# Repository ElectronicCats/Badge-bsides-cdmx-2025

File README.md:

# Security BSides CDMX 2025 Badge

## Technology

- Puya PY32F030F28U6TR
- Neopixels
- Display OLED
- 2x AAA Battery Holder
- Shitty Addon Connector

## Getting Started

Your badge comes with a pre-installed firmware, but in case you need to reprogram it, you can use the binaries from the release section.

If you want to build your own firmware, check out the [README](firmware/README.md) in the firmware folder.

## Gratitude
Do you want to say thank you? Tag these companies on social networks and show them your badge, thanks to them it is possible

- [Electronic Cats](https://electroniccats.com/)
- [BSides CDMX](https://bsidescdmx.org/)

## License

Electronic Cats invests time and resources providing this open source design, please support Electronic Cats and open-source hardware by purchasing products from Electronic Cats!

Designed by Electronic Cats.

Hardware released under an CERN Open Hardware Licence v1.2. See the LICENSE_HARDWARE file for more information.

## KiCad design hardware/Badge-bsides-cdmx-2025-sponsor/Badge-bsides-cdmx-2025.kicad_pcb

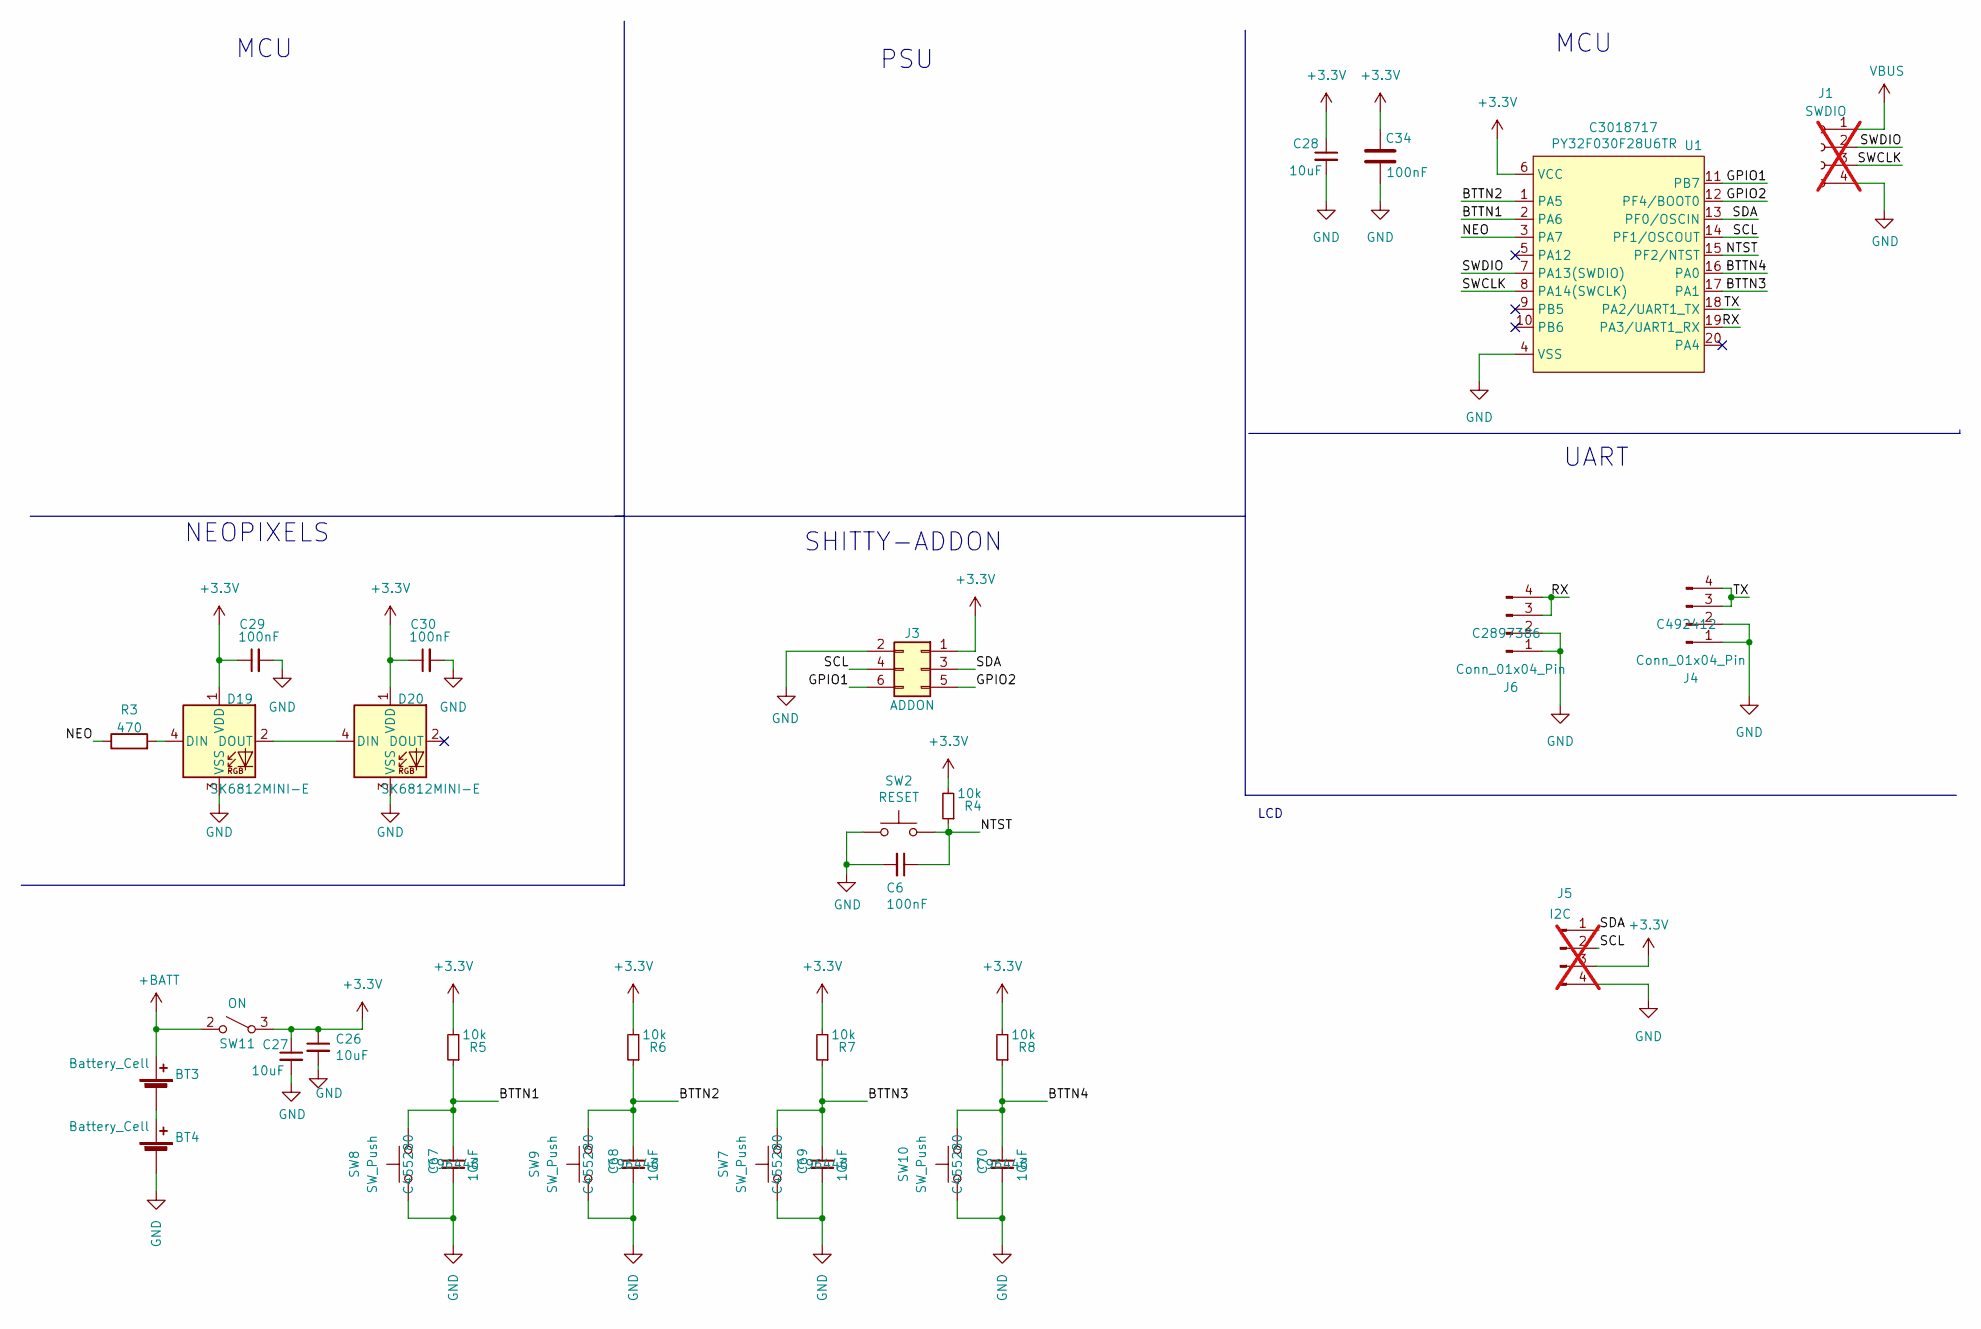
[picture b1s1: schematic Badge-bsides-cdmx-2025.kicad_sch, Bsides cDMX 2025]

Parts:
BT3, BT4: Battery_Cell; BatteryHolder_Keystone_2466_1xAAA; LCSC# C5290189
C6, C29, C30, C34: 100nF; C_0603_1608Metric; LCSC# C66501
C26, C27, C28, C67, C68, C69, C70: 10uF; C_0603_1608Metric; LCSC# C96446
D19, D20: SK6812MINI-E; LED_SK6812-E; LCSC# C5149201
J1: SWDIO; PinHeader_1x04_P2.54mm_Vertical; not fitted
J3: ADDON; PinSocket_2x03_P2.54mm_Vertical_SMD; LCSC# C3975148
J4: Conn_01x04_Pin; PinHeader_1x04_P2.54mm_Horizontal; LCSC# C492412
J5: I2C; PinSocket_1x04_P2.54mm_Vertical; not fitted
J6: Conn_01x04_Pin; PinSocket_1x04_P2.54mm_Horizontal; LCSC# C2897386
R3: 470; R_0603_1608Metric; LCSC# C114669
R4, R5, R6, R7, R8: 10k; R_0603_1608Metric; LCSC# C99198
SW2: RESET; SW_SPST_TL3342; LCSC# C318884
SW7, SW8, SW9, SW10: SW_Push; TS1088R02026; LCSC# C455280
SW11: ON; JS102011SAQN; LCSC# C221660
U1: PY32F030F28U6TR; QFN-20-1EP_3x3mm_P0.4mm_EP1.65x1.65mm_ThermalVias; LCSC# C3018717

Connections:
+3.3V: C26.1, C27.1, C28.1, C29.1, C30.1, C34.1, D19.1 (VDD), D20.1 (VDD), J3.1, J5.3, R4.2, R5.2, R6.2, R7.2, R8.2, SW11.3 (A), U1.6 (VCC)
+BATT: BT3.2 (+), SW11.2 (B)
/BTTN1: C67.1, R5.1, SW8.2, U1.2 (PA6)
/BTTN2: C68.1, R6.1, SW9.2, U1.1 (PA5)
/BTTN3: C69.1, R7.1, SW7.2, U1.17 (PA1)
/BTTN4: C70.1, R8.1, SW10.2, U1.16 (PA0)
/GPIO1: J3.6, U1.11 (PB7)
/GPIO2: J3.5, U1.12 (PF4/BOOT0)
/NEO: R3.1, U1.3 (PA7)
/NTST: C6.1, R4.1, SW2.2, U1.15 (PF2/NTST)
/RX: J6.3, J6.4, U1.19 (PA3/UART1_RX)
/SCL: J3.4, J5.2, U1.14 (PF1/OSCOUT)
/SDA: J3.3, J5.1, U1.13 (PF0/OSCIN)
/SWCLK: J1.3, U1.8 (PA14(SWCLK))
/SWDIO: J1.2, U1.7 (PA13(SWDIO))
/TX: J4.3, J4.4, U1.18 (PA2/UART1_TX)
GND: BT4.2 (-), C6.2, C26.2, C27.2, C28.2, C29.2, C30.2, C34.2, C67.2, C68.2, C69.2, C70.2, D19.3 (VSS), D20.3 (VSS), J1.4, J3.2, J4.1, J4.2, J5.4, J6.1, J6.2, SW2.1, SW7.1, SW8.1, SW9.1, SW10.1, U1.4 (VSS), U1.21 (VSS)
unnamed: BT3.1 (-), BT4.1 (+)
unnamed: D19.4 (DIN), R3.2
unnamed: D19.2 (DOUT), D20.4 (DIN)
VBUS: J1.1

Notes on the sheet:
LCD
SHITTY-ADDON
MCU
UART
PSU
NEOPIXELS

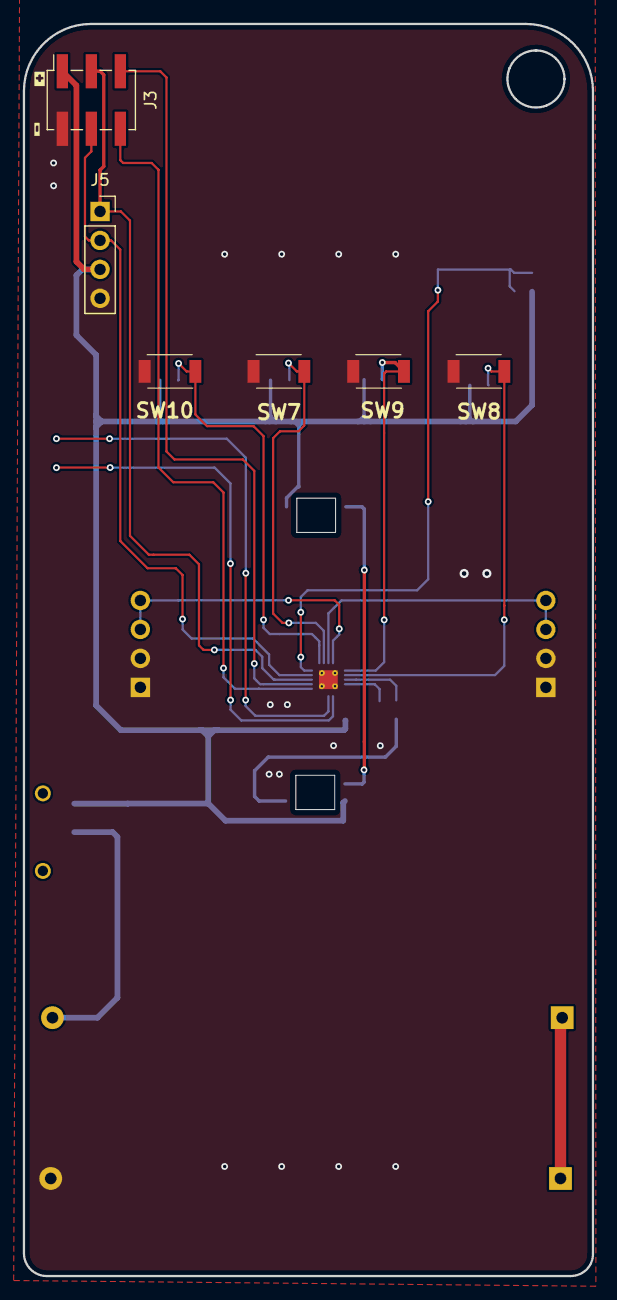
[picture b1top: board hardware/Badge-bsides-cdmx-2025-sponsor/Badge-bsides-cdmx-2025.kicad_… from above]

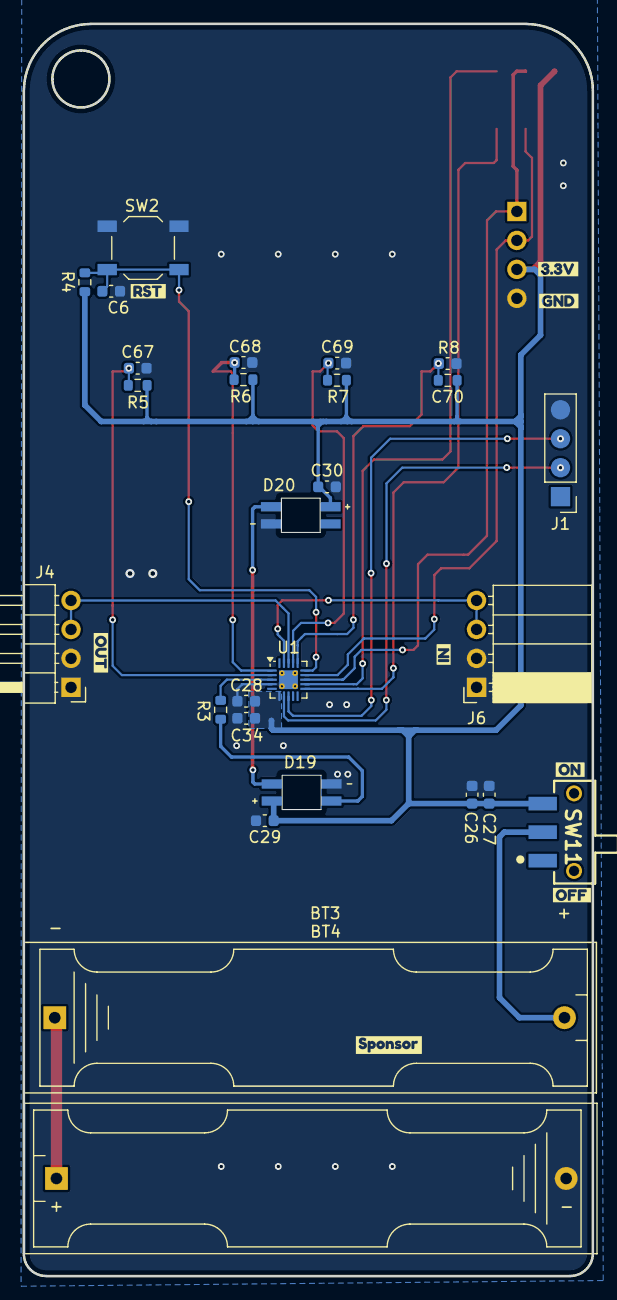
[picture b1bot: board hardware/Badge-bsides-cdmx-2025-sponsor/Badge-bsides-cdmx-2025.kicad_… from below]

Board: 2 copper layers, 49.9 x 109.8 mm, 43 parts (35 on the bottom side), 20 nets.

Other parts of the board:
kibuzzard-6841DC13: G***; kibuzzard-6841DC13
kibuzzard-6842C085: G***; kibuzzard-6842C085
kibuzzard-6842ED2D: G***; kibuzzard-6842ED2D
kibuzzard-6842ED45: G***; kibuzzard-6842ED45
kibuzzard-6842EE28: G***; kibuzzard-6842EE28
kibuzzard-6842EE36: G***; kibuzzard-6842EE36
kibuzzard-684316B7: G***; kibuzzard-684316B7
kibuzzard-684316C2: G***; kibuzzard-684316C2
kibuzzard-684316CB: G***; kibuzzard-684316CB
kibuzzard-684316D5: G***; kibuzzard-684316D5

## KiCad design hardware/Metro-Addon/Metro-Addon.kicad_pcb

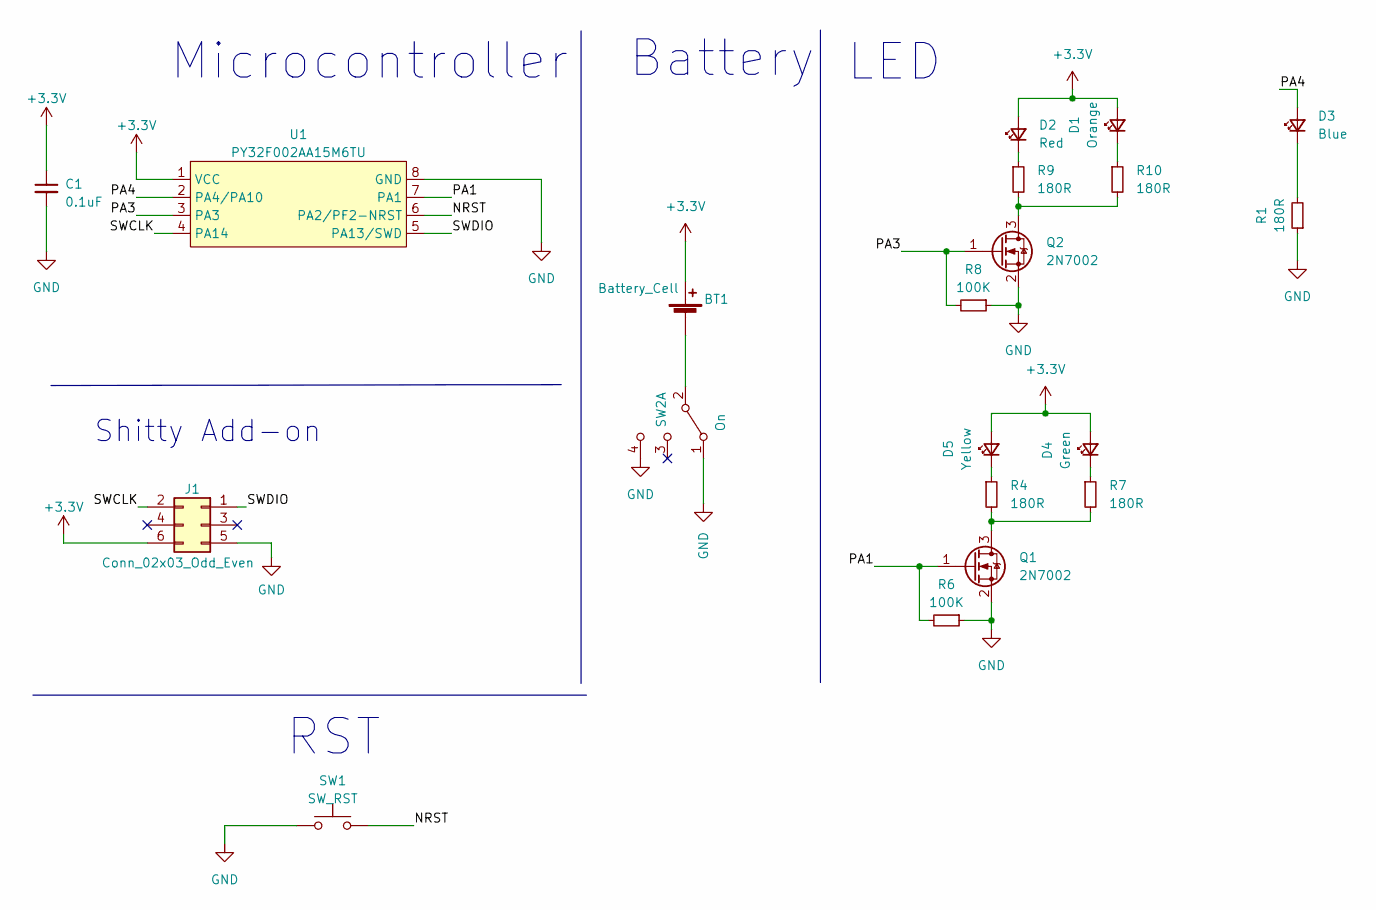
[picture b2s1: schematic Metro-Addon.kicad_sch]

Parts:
BT1: Battery_Cell; BAT-HLD-001; LCSC# C964833
C1: 0.1uF; C_0805_2012Metric; LCSC# C235731
D1: Orange; LED_0805_2012Metric; LCSC# C434437
D2: Red; LED_0805_2012Metric; LCSC# C965812
D3: Blue; LED_0805_2012Metric; LCSC# C205441
D4: Green; LED_0805_2012Metric; LCSC# C965815
D5: Yellow; LED_0805_2012Metric; LCSC# C84261
J1: Conn_02x03_Odd_Even; B-2100N06P-B111_CKM; LCSC# C780054
Q1, Q2: 2N7002; SOT-23; LCSC# C8545
R1, R4, R7, R9, R10: 180R; R_0805_2012Metric; LCSC# C1339
R6, R8: 100K; R_0805_2012Metric; LCSC# C96346
SW1: SW_RST; SW_SPST_TL3342; LCSC# C318889
SW2: On; MSK12C02; LCSC# C431540
U1: PY32F002AA15M6TU; PY32F002AL15S6TU; LCSC# C5292060

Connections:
+3.3V: BT1.2 (+), C1.1, D1.2 (A), D2.2 (A), D4.2 (A), D5.2 (A), J1.6, U1.1 (VCC)
/NRST: SW1.2, U1.6 (PA2/PF2-NRST)
/PA1: Q1.1 (G), R6.2, U1.7 (PA1)
/PA3: Q2.1 (G), R8.2, U1.3 (PA3)
/PA4: D3.2 (A), U1.2 (PA4/PA10)
/SWCLK: J1.2, U1.4 (PA14)
/SWDIO: J1.1, U1.5 (PA13/SWD)
GND: C1.2, J1.5, Q1.2 (S), Q2.2 (S), R1.1, R6.1, R8.1, SW1.1, SW2.1 (A), SW2.4 (C), U1.8 (GND)
unnamed: BT1.1 (-), SW2.2 (B)
unnamed: D1.1 (K), R10.1
unnamed: D2.1 (K), R9.1
unnamed: D3.1 (K), R1.2
unnamed: D4.1 (K), R7.1
unnamed: D5.1 (K), R4.1
unnamed: Q1.3 (D), R4.2, R7.2
unnamed: Q2.3 (D), R9.2, R10.2

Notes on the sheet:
Microcontroller
LED
RST
Battery
Shitty Add-on

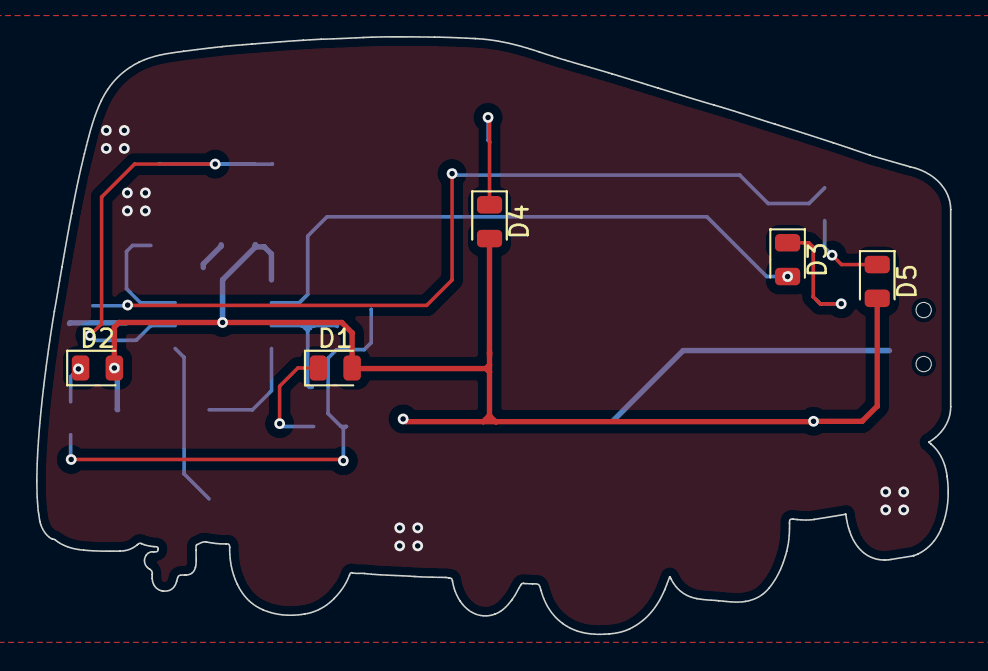
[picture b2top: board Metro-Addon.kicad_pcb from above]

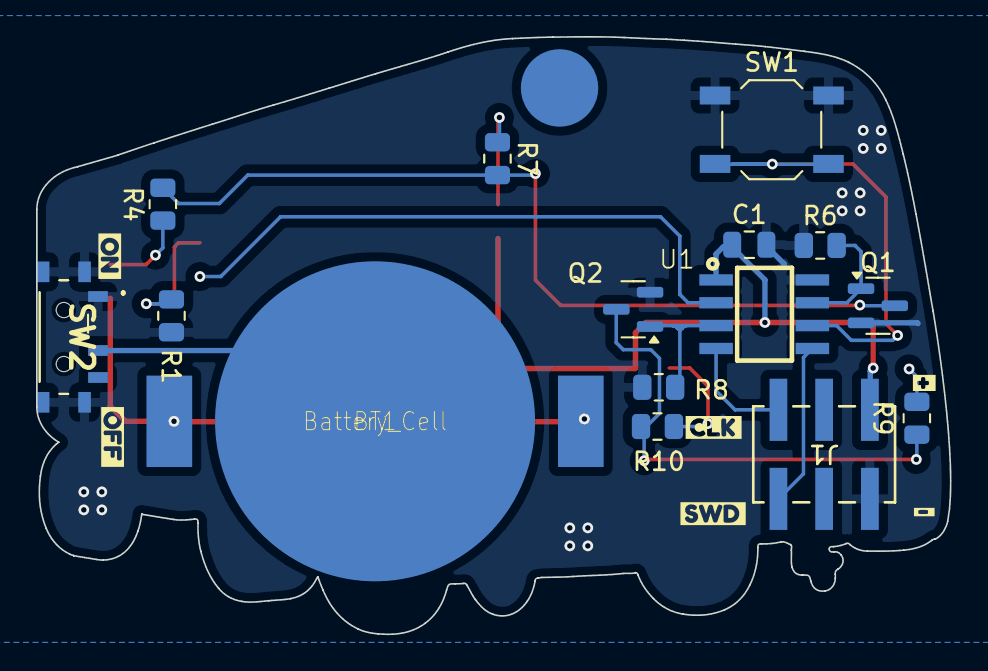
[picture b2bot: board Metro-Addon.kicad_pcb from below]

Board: 2 copper layers, 50.8 x 33.2 mm, 26 parts (21 on the bottom side), 16 nets.

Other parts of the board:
kibuzzard-684752D8: G***; kibuzzard-684752D8
kibuzzard-684752FB: G***; kibuzzard-684752FB
kibuzzard-684756AF: G***; kibuzzard-684756AF
kibuzzard-684756BD: G***; kibuzzard-684756BD
kibuzzard-684756E4: G***; kibuzzard-684756E4
kibuzzard-684756F0: G***; kibuzzard-684756F0

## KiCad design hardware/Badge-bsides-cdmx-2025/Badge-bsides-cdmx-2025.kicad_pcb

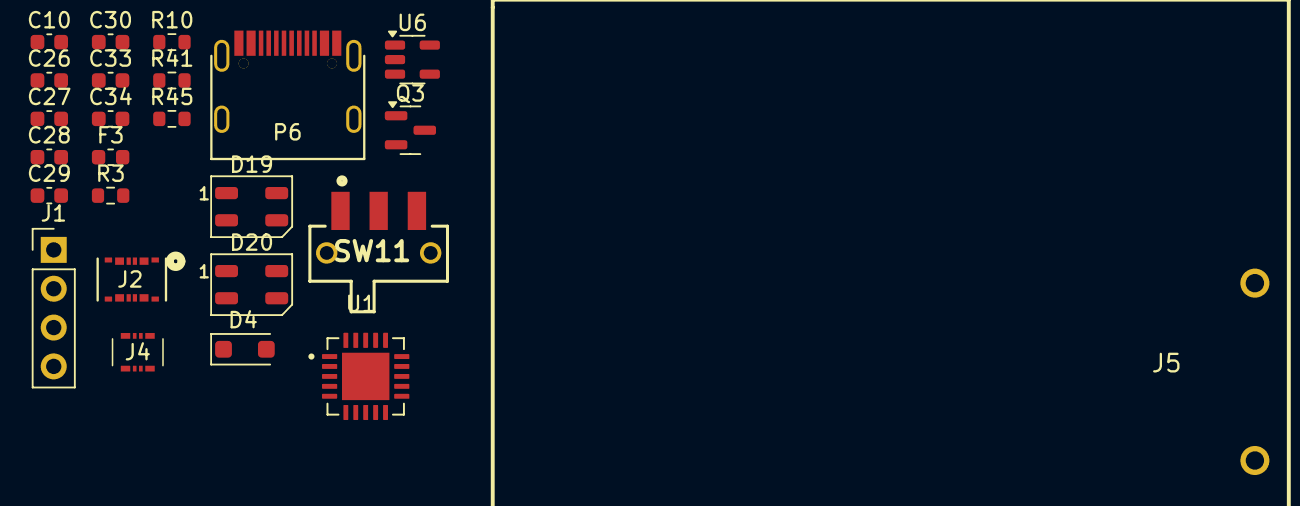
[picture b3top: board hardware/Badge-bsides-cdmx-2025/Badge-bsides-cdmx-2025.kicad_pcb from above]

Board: 2 copper layers, 25 parts (0 on the bottom side), 17 nets, no tracks yet.

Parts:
C10, C26, C27, C28: 10uF; C_0603_1608Metric
C29, C30, C33, C34: 100nF; C_0603_1608Metric
D4: MBR120; D_SOD-123F
D19, D20: WS2812B; LED_WS2812B-Mini_PLCC4_3.5x3.5mm
F3: 750mA; Fuse_0603_1608Metric
J1: SWDIO; PinHeader_1x04_P2.54mm_Vertical
J2: Conn_01x08_Pin; CONN8_505004-0812_MOL
J4: Conn_01x02_Pin; 5050060812
J5: Battery; BAT-TH_BH-AAA-A1AJ024
P6: USB_C_Plug_USB2.0; C393939
Q3: DMG3415U-7; SOT-23
R3: 1K; R_0603_1608Metric
R10: 100K; R_0603_1608Metric
R41, R45: 5k1; R_0603_1608Metric
SW11: ON; JS102011SAQN
U1: PY32F030F28U6TR; QFN65P500X500X80-21N
U6: AP2112K-3.3; SOT-23-5

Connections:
+3.3V: C28.1, C34.1, U1.6 (VCC)
+3V3: C26.1, C29.1, C30.1, D19.1 (VDD), D20.1 (VDD), U6.5 (VOUT)
+BATT: J5.1, Q3.3 (D)
/NEOPIXELES: R3.1, U1.3 (PA7)
/RX: J2.2, J2.3, J2.6, J2.7, U1.19 (PA3/UART1_RX)
/SWCLK: J1.3, U1.8 (PA14(SWCLK))
/SWDIO: J1.2, U1.7 (PA13(SWDIO))
/TX: J4.2, J4.3, J4.6, J4.7, U1.18 (PA2/UART1_TX)
GND: C10.2, C26.2, C27.2, C28.2, C29.2, C30.2, C33.2, C34.2, D19.3 (VSS), D20.3 (VSS), J1.4, J2.1, J2.4, J2.5, J2.8, J4.1, J4.4, J4.5, J4.8, J5.2, P6.A1 (GND), P6.S1 (SHIELD), R10.2, R41.1, R45.1, U1.4 (VSS), U6.2 (GND)
unnamed: D4.1 (K), Q3.2 (S), SW11.3 (A)
unnamed: D19.4 (DIN), R3.2
unnamed: D19.2 (DOUT), D20.4 (DIN)
unnamed: F3.1, P6.A4 (VBUS)
unnamed: P6.A5 (CC), R41.2
unnamed: P6.B5 (VCONN), R45.2
unnamed: C10.1, SW11.2 (B), U6.1 (VIN), U6.3 (EN)
VBUS: C33.1, D4.2 (A), F3.2, J1.1, Q3.1 (G), R10.1

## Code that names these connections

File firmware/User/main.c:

/***
 * Demo: I2C - SSD1306 OLED
 *
 * PY32          SSD1306
 *  PF1/PA9       SCL
 *  PF0/PA10      SDA
 */
#include "main.h"
#include <string.h>
#include "bitmaps.h"
#include "buttons.h"
#include "menu.h"
#include "py32f0xx_bsp_clock.h"
#include "py32f0xx_bsp_printf.h"
#include "ssd1306.h"
#include "ws2812_spi.h"

#define I2C_ADDRESS 0xA0 /* host/client address */
#define I2C_STATE_READY 0
#define I2C_STATE_BUSY_TX 1
#define I2C_STATE_BUSY_RX 2

__IO uint32_t i2cState = I2C_STATE_READY;

static void APP_I2C_Config(void);
static void APP_GPIO_Config(void);
static void APP_SPIConfig(void);

int main(void) {
  uint8_t i = 0, r = 0, g = 0x60, b = 0xC0;
  BSP_RCC_HSI_24MConfig();

  BSP_USART_Config(115200);
  printf("I2C Demo: \r\nClock: %ld\r\n", SystemCoreClock);

  APP_I2C_Config();
  APP_GPIO_Config();
  APP_SPIConfig();

  uint8_t res = SSD1306_Init();
  printf("OLED init: %s\n", res == 0 ? "ERROR" : "OK");

  SSD1306_UpdateScreen();
  SSD1306_DrawBitmap(epd_bitmap_bsides_logo, 0, 0, 128, 32);
  SSD1306_UpdateScreen();

  // Wait for any button press
  while (1) {
    if (is_btn_back_pressed()) {
      break;
    }
    if (is_btn_enter_pressed()) {
      break;
    }
    if (is_btn_down_pressed()) {
      break;
    }
    if (is_btn_up_pressed()) {
      break;
    }
    i = (i + 1) % WS2812_NUM_LEDS;
    ws2812_pixel(i, r++, g++, b++);
    LL_mDelay(10);
  }
  
  while (1) {
    Menu_UpdateAndRender();
  }
}

static void APP_GPIO_Config(void) {
  LL_GPIO_InitTypeDef GPIO_InitStruct = {0};

  LL_IOP_GRP1_EnableClock(LL_IOP_GRP1_PERIPH_GPIOA);

  /*
   * Buttons:
   * DOWN:  PA0
   * UP:    PA1
   * BACK:  PA5
   * ENTER: PA6
   */
  GPIO_InitStruct.Pin = LL_GPIO_PIN_0 | LL_GPIO_PIN_1 | LL_GPIO_PIN_5 | LL_GPIO_PIN_6;
  GPIO_InitStruct.Mode = LL_GPIO_MODE_INPUT;
  GPIO_InitStruct.Pull = LL_GPIO_PULL_UP;
  LL_GPIO_Init(GPIOA, &GPIO_InitStruct);
}

static void APP_I2C_Config(void) {
  LL_GPIO_InitTypeDef GPIO_InitStruct = {0};

  LL_IOP_GRP1_EnableClock(LL_IOP_GRP1_PERIPH_GPIOF);
  LL_APB1_GRP1_EnableClock(LL_APB1_GRP1_PERIPH_I2C1);

  /**
   * SCL: PF1 & AF_12, PA9 & AF_6
   * SDA: PF0 & AF_12, PA10 & AF_6
   *
   * Change pins to PF1 / PF0 for parts have no PA9 / PA10
   */
  // PF1 SCL
  GPIO_InitStruct.Pin = LL_GPIO_PIN_1;
  GPIO_InitStruct.Mode = LL_GPIO_MODE_ALTERNATE;
  GPIO_InitStruct.Speed = LL_GPIO_SPEED_FREQ_HIGH;
  GPIO_InitStruct.OutputType = LL_GPIO_OUTPUT_OPENDRAIN;
  GPIO_InitStruct.Pull = LL_GPIO_PULL_UP;
  GPIO_InitStruct.Alternate = LL_GPIO_AF_12;
  LL_GPIO_Init(GPIOF, &GPIO_InitStruct);

  // PF0 SDA
  GPIO_InitStruct.Pin = LL_GPIO_PIN_0;
  GPIO_InitStruct.Alternate = LL_GPIO_AF_12;
  LL_GPIO_Init(GPIOF, &GPIO_InitStruct);

  LL_APB1_GRP1_ForceReset(LL_APB1_GRP1_PERIPH_I2C1);
  LL_APB1_GRP1_ReleaseReset(LL_APB1_GRP1_PERIPH_I2C1);

  LL_I2C_InitTypeDef I2C_InitStruct;
  /*
   * Clock speed:
   * - standard = 100khz, if PLL is on, set system clock <= 16MHz, or i2c cannot work normally
   * - fast     = 400khz
   */
  I2C_InitStruct.ClockSpeed = LL_I2C_MAX_SPEED_FAST;
  I2C_InitStruct.DutyCycle = LL_I2C_DUTYCYCLE_16_9;
  I2C_InitStruct.OwnAddress1 = I2C_ADDRESS;
  I2C_InitStruct.TypeAcknowledge = LL_I2C_NACK;
  LL_I2C_Init(I2C1, &I2C_InitStruct);

  /* Enale clock stretch (reset default: on) */
  // LL_I2C_EnableClockStretching(I2C1);

  /* Enable general call (reset default: off) */
  // LL_I2C_EnableGeneralCall(I2C1);
}

void APP_I2C_Transmit(uint8_t devAddress, uint8_t memAddress, uint8_t* pData, uint16_t len) {
  while (i2cState == I2C_STATE_BUSY_TX)
    ;

  LL_I2C_DisableBitPOS(I2C1);

  i2cState = I2C_STATE_BUSY_TX;

  /* Start */
  LL_I2C_GenerateStartCondition(I2C1);
  while (LL_I2C_IsActiveFlag_SB(I2C1) != 1)
    ;
  /* Send slave address */
  LL_I2C_TransmitData8(I2C1, (devAddress & (uint8_t)(~0x01)));
  while (LL_I2C_IsActiveFlag_ADDR(I2C1) != 1)
    ;
  LL_I2C_ClearFlag_ADDR(I2C1);

  /* Send memory address */
  LL_I2C_TransmitData8(I2C1, memAddress);
  while (LL_I2C_IsActiveFlag_BTF(I2C1) != 1)
    ;

  /* Transfer data */
  while (len > 0) {
    while (LL_I2C_IsActiveFlag_TXE(I2C1) != 1)
      ;
    LL_I2C_TransmitData8(I2C1, *pData++);
    len--;

    if ((LL_I2C_IsActiveFlag_BTF(I2C1) == 1) && (len != 0U)) {
      LL_I2C_TransmitData8(I2C1, *pData++);
      len--;
    }

    while (LL_I2C_IsActiveFlag_BTF(I2C1) != 1)
      ;
  }

  /* Stop */
  LL_I2C_GenerateStopCondition(I2C1);
  i2cState = I2C_STATE_READY;
}

uint8_t SPI_TxRxByte(uint8_t data)
{
  uint8_t SPITimeout = 0xFF;
  /* Check the status of Transmit buffer Empty flag */
  while (READ_BIT(SPI1->SR, SPI_SR_TXE) == RESET)
  {
    if (SPITimeout-- == 0) return 0;
  }
  LL_SPI_TransmitData8(SPI1, data);
  SPITimeout = 0xFF;
  while (READ_BIT(SPI1->SR, SPI_SR_RXNE) == RESET)
  {
    if (SPITimeout-- == 0) return 0;
  }
  // Read from RX buffer
  return LL_SPI_ReceiveData8(SPI1);
}

static void APP_SPIConfig(void)
{
  LL_SPI_InitTypeDef SPI_InitStruct = {0};
  LL_GPIO_InitTypeDef GPIO_InitStruct = {0};

  LL_IOP_GRP1_EnableClock(LL_IOP_GRP1_PERIPH_GPIOA);
  LL_APB1_GRP2_EnableClock(LL_APB1_GRP2_PERIPH_SPI1);

  // PA7 MOSI
  GPIO_InitStruct.Pin = LL_GPIO_PIN_7;
  GPIO_InitStruct.Mode = LL_GPIO_MODE_ALTERNATE;
  GPIO_InitStruct.Speed = LL_GPIO_SPEED_FREQ_HIGH;
  GPIO_InitStruct.OutputType = LL_GPIO_OUTPUT_PUSHPULL;
  GPIO_InitStruct.Pull = LL_GPIO_PULL_NO;
  GPIO_InitStruct.Alternate = LL_GPIO_AF_0;
  LL_GPIO_Init(GPIOA, &GPIO_InitStruct);

  /* The frequency after prescaler should be below 8.25MHz */
  SPI_InitStruct.BaudRate = LL_SPI_BAUDRATEPRESCALER_DIV8;
  SPI_InitStruct.TransferDirection = LL_SPI_FULL_DUPLEX;
  SPI_InitStruct.Mode = LL_SPI_MODE_MASTER;
  SPI_InitStruct.DataWidth = LL_SPI_DATAWIDTH_8BIT;
  SPI_InitStruct.ClockPolarity = LL_SPI_POLARITY_LOW;
  SPI_InitStruct.ClockPhase = LL_SPI_PHASE_1EDGE;
  SPI_InitStruct.NSS = LL_SPI_NSS_SOFT;
  SPI_InitStruct.BitOrder = LL_SPI_MSB_FIRST;
  LL_SPI_Init(SPI1, &SPI_InitStruct);
  LL_SPI_Enable(SPI1);
}

void APP_ErrorHandler(void) {
  while (1)
    ;
}

#ifdef USE_FULL_ASSERT
void assert_failed(uint8_t* file, uint32_t line) {
  while (1)
    ;
}
#endif /* USE_FULL_ASSERT */

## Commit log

2025-06-02 Feat(Hw): SCH_0.1v
2025-06-02 FIx(Hw): Fixed_Bom_and_footprints
2025-06-03 feat: update gitignore
2025-06-03 feat: add button RST and shitty connector
2025-06-05 feat(Hw): Floorplan draft
2025-06-05 feat(Hw):started_routing
2025-06-05 feat(Hw):Route_Sponsor
2025-06-06 feat(Hw):Route_Community
2025-06-06 feat(Hw):Neopixels_Added_Staff
2025-06-06 feat(Hw):Neopixels_added(sponsor)
2025-06-06 Feat(Hw): Fixed_Bom(Sponsor,guest)
2025-06-06 Feat(Hw): FIxed_neopixels_bom(Sponsor,guest)
2025-06-06 Auto stash before merge of "main" and "origin/main"
2025-06-06 Fix(Hw): Fixed_BOM(Staff,Community, Speaker)
2025-06-06 feat(Hw):Community_Badge_Added_Neopixels
2025-06-06 feat(Hw):Update_BOM_And_Route
2025-06-06 feat(HW):Staff_Updated
2025-06-06 feat(Hw):BoM_Updated_Staff_Community
2025-06-06 feat:remove usb staff
2025-06-06 fix: vbus ok staff
2025-06-06 feat(Hw)USB_C_Deleted
2025-06-06 fix(Hw):Connectors_Moved
2025-06-06 feat(hw): add metro-addon project
2025-06-06 feat(Hw):Update_Route
2025-06-06 feat(hw): add schematic in metro-addon
2025-06-06 feat(Hw):Update_Labels
2025-06-07 fix(Hw):sponsor_and_Community_updated
2025-06-07 feat(hw): add routes in metro addon
2025-06-09 feat(Hw):Labels-Added
2025-06-09 feat(Hw):Led_Modified
2025-06-10 feat(Hw):Update_BOM
2025-06-10 feat(Hw):Mounting_Hole_Added
2025-06-11 fix(Hw):Labels_Updated
2025-06-11 fix(Hw):Ground_and_neopixel_resistor(sponsor)
2025-06-17 chore: add base firmware project
2025-06-17 chore: add firmware build dir
2025-06-17 docs: add readme info
2025-06-17 chore: make relative paths
2025-06-17 chore: add .env file
2025-06-17 docs: setup toolchain path
2025-06-19 chore: use arm toolchain from env file
2025-06-19 feat: add ssd1306 support
2025-06-20 refactor: code style
2025-06-20 feat: display bsides logo at startup
2025-06-20 feat: add draw bitmap function
2025-06-20 fix: flat content on screen
2025-06-21 feat: configure navigation buttons
2025-06-23 feat: add menu system
2025-06-24 fix: pressed buttons
2025-06-24 feat: add waiting for connection screen
2025-06-25 feat: add uart listener
2025-06-25 fix: end of line char
2025-06-25 feat: add neopixels support
2025-06-26 feat: add brightness control
2025-06-27 feat: add turn on/off settings for neopixels
2025-06-27 fix: neopixels animation on all menus
2025-06-27 feat: make menu items scrollable
2025-06-30 feat: sync colors through serial messages
2025-06-30 feat(Fw):Init_Firmware_Metro
2025-07-01 refactor: found badge text
2025-07-01 refactor: credits text
2025-07-01 chore: add license files
2025-07-01 feat: add user brightness control
2025-07-02 fix: unable to turn on leds after turn off
2025-07-02 feat: add solid and rainbow options
2025-07-02 feat: replace breathing by mexican flag animation
2025-07-02 fix: syncronize animations across badges
2025-07-02 fix: cannot select other animation after selecting solid color
2025-07-02 fix: current animation do not work on main menu
2025-07-02 docs: update title, technology, and getting started description
2025-07-02 fix: real time brightness control
